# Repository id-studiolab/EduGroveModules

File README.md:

# EduGroveModules

A collection of Grove-compatible modules, designed specifically for educational needs. 

<div style="display: flex; flex-direction: row; flex-wrap: wrap; justify-content: center;">

  </a>
    
  </a>
    
</div>

## Grove-Compatible Modules for Education

These designs are tailored for use in the [**Connected Interaction Kit**](https://id-studiolab.github.io/Connected-Interaction-Kit) and beyond, offering specific functionalities and optimizations to enhance hands-on learning in tech and design education.

## Modules Overview

### [**Custom Component Board**](CustomComponents/README.md)

A versatile 2x3 cm PCB for easy assembly and interfacing of common sensors, demanding basic soldering skills. Useful for educational soldering practices.

### [**Time-of-Flight Distance Sensor**](Time-of-Flight/README.md)

Cost-effective, Grove-compatible boards for the VL53L0X sensor, enabling precise distance measurements up to 2 meters.

### [**ChaiNEO**](ChaiNEO/README.md)

Daisy-chainable, Grove-compatible boards designed for Neopixel-compatible LEDs.

### [**Motor Driver**](MotorDriver/README.md)

Simple I2C motor driver for servo,DC, and stepper motors.

### [**High power Neopixel**](HighPowerNEO/README.md)

A 12W neopixel with extra white chip for accurate color reproduction.

### [**Presence Sensor**](RadarSensor/README.md)

An adapter board for the LD2410 or LD2450 to make it Grove compatible for the Itsy Bitsy.

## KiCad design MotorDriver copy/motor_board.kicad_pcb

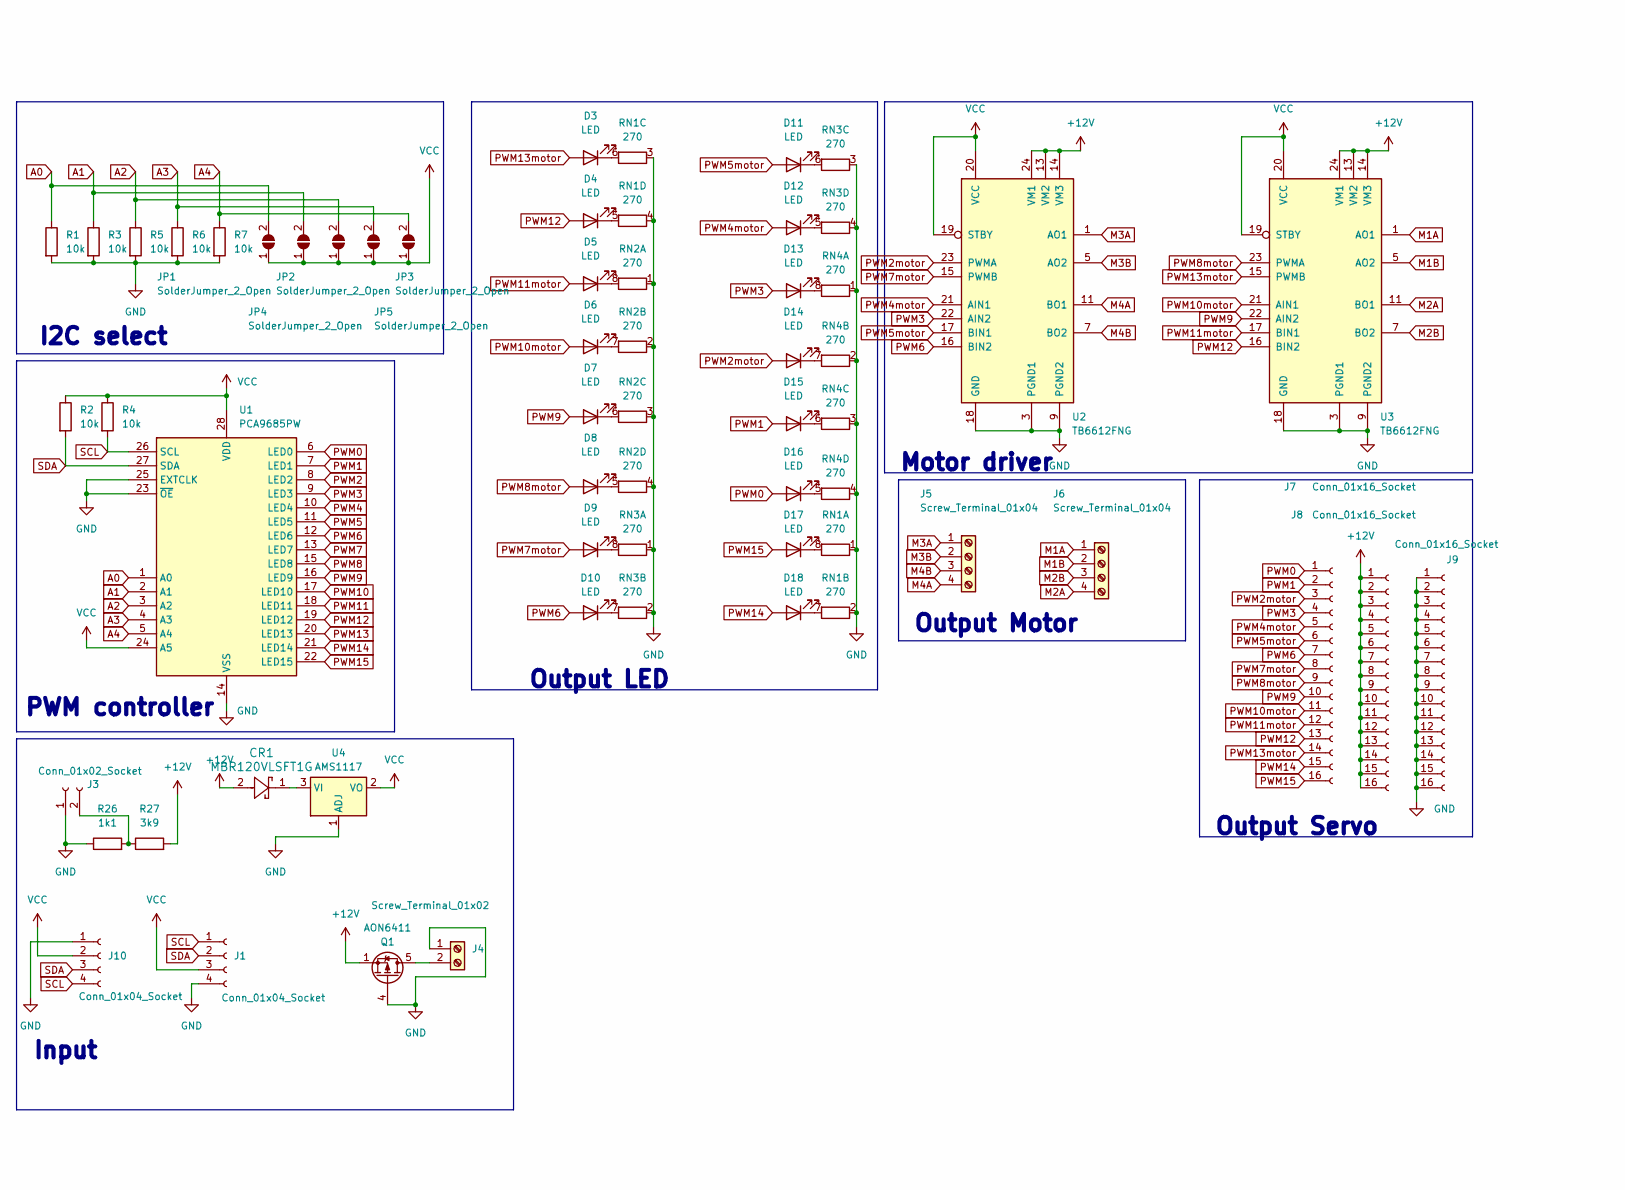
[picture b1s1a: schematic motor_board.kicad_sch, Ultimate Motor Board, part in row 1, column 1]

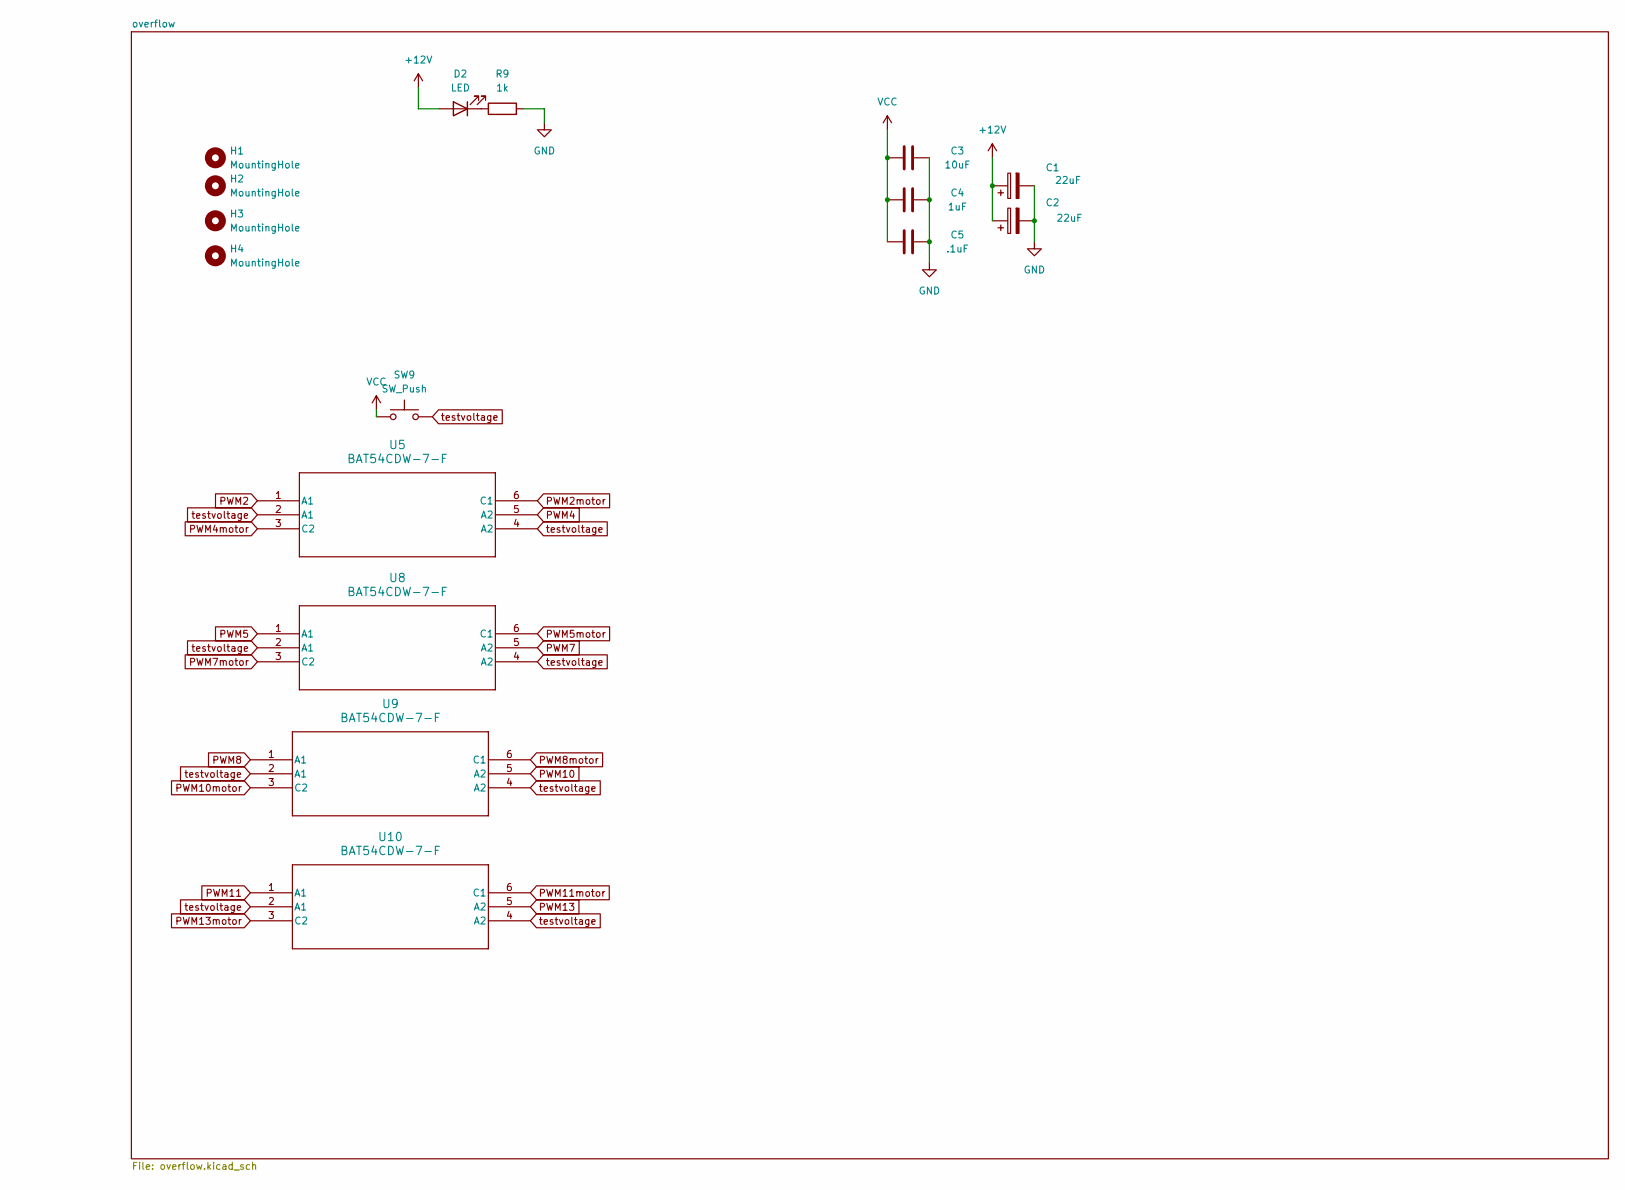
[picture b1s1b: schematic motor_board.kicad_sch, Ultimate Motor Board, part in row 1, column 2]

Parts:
C1, C2: 22uF; CP_Elec_6.3x5.7
C3: 10uF; C_0805_2012Metric_Pad1.18x1.45mm_HandSolder
C4: 1uF; C_0805_2012Metric_Pad1.18x1.45mm_HandSolder
C5: .1uF; C_0805_2012Metric_Pad1.18x1.45mm_HandSolder
CR1: MBR120VLSFT1G; SDO_SOD-123FL_ONS
D2, D3, D4, D5, D6, D7, D8, D9, D10, D11, D12, D13, D14, D15, D16, D17, D18: LED; LED_0805_2012Metric_Pad1.15x1.40mm_HandSolder
H1, H2, H3, H4: MountingHole; MountingHole_2.5mm
J1: Conn_01x04_Socket; NS-Tech_Grove_1x04_P2mm_Vertical
J3: Conn_01x02_Socket; PinHeader_1x02_P2.54mm_Vertical
J4: Screw_Terminal_01x02; TerminalBlock_Phoenix_PT-1,5-2-5.0-H_1x02_P5.00mm_Horizontal
J5, J6: Screw_Terminal_01x04; TerminalBlock_Phoenix_PT-1,5-4-5.0-H_1x04_P5.00mm_Horizontal
J7, J8, J9: Conn_01x16_Socket; PinHeader_1x16_P2.54mm_Vertical
J10: Conn_01x04_Socket; JST_SH_SM04B-SRSS-TB_1x04-1MP_P1.00mm_Horizontal
JP1, JP2, JP3, JP4, JP5: SolderJumper_2_Open; SolderJumper-2_P1.3mm_Open_TrianglePad1.0x1.5mm
Q1: AON6411; AO_DFN-8-1EP_5.55x5.2mm_P1.27mm_EP4.12x4.6mm
R1, R2, R3, R4, R5, R6, R7: 10k; R_0805_2012Metric_Pad1.20x1.40mm_HandSolder
R9: 1k; R_0805_2012Metric_Pad1.20x1.40mm_HandSolder
R26: 1k1; R_0805_2012Metric_Pad1.20x1.40mm_HandSolder
R27: 3k9; R_0805_2012Metric_Pad1.20x1.40mm_HandSolder
RN1, RN2, RN3, RN4: 270; R_Array_Convex_4x1206
SW9: SW_Push; SW_Push_SPST_NO_Alps_SKRK
U1: PCA9685PW; TSSOP-28_4.4x9.7mm_P0.65mm
U2, U3: TB6612FNG; SSOP-24_5.3x8.2mm_P0.65mm
U4: AMS1117; SOT-223-3_TabPin2
U5, U8, U9, U10: BAT54CDW-7-F; SOT-363_DIO

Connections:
+12V: C1.1, C2.1, CR1.2, D2.2 (A), J8.1, J8.2, J8.3, J8.4, J8.5, J8.6, J8.7, J8.8, J8.9, J8.10, J8.11, J8.12, J8.13, J8.14, J8.15, J8.16, Q1.1 (S), Q1.2 (S), Q1.3 (S), R27.2, U2.13 (VM2), U2.14 (VM3), U2.24 (VM1), U3.13 (VM2), U3.14 (VM3), U3.24 (VM1)
A0: JP1.2 (B), R1.1, U1.1 (A0)
A1: JP2.2 (B), R3.1, U1.2 (A1)
A2: JP3.2 (B), R5.1, U1.3 (A2)
A3: JP4.2 (B), R6.1, U1.4 (A3)
A4: JP5.2 (B), R7.1, U1.5 (A4)
GND: C1.2, C2.2, C3.2, C4.2, C5.2, J1.4, J3.1, J4.1, J9.1, J9.2, J9.3, J9.4, J9.5, J9.6, J9.7, J9.8, J9.9, J9.10, J9.11, J9.12, J9.13, J9.14, J9.15, J9.16, J10.1, Q1.4 (G), R1.2, R3.2, R5.2, R6.2, R7.2, R9.2, R26.1, RN1.1 (R1.1), RN1.2 (R2.1), RN1.3 (R3.1), RN1.4 (R4.1), RN2.1 (R1.1), RN2.2 (R2.1), RN2.3 (R3.1), RN2.4 (R4.1), RN3.1 (R1.1), RN3.2 (R2.1), RN3.3 (R3.1), RN3.4 (R4.1), RN4.1 (R1.1), RN4.2 (R2.1), RN4.3 (R3.1), RN4.4 (R4.1), U1.14 (VSS), U1.23 (~OE), U1.25 (EXTCLK), U2.3 (PGND1), U2.4 (PGND1), U2.9 (PGND2), U2.10 (PGND2), U2.18 (GND), U3.3 (PGND1), U3.4 (PGND1), U3.9 (PGND2), U3.10 (PGND2), U3.18 (GND), U4.1 (ADJ)
M1A: J6.1, U3.1 (AO1), U3.2 (AO1)
M1B: J6.2, U3.5 (AO2), U3.6 (AO2)
M2A: J6.4, U3.11 (BO1), U3.12 (BO1)
M2B: J6.3, U3.7 (BO2), U3.8 (BO2)
M3A: J5.1, U2.1 (AO1), U2.2 (AO1)
M3B: J5.2, U2.5 (AO2), U2.6 (AO2)
M4A: J5.4, U2.11 (BO1), U2.12 (BO1)
M4B: J5.3, U2.7 (BO2), U2.8 (BO2)
unnamed: D2.1 (K), R9.1
unnamed: D3.1 (K), RN1.6 (R3.2)
unnamed: D4.1 (K), RN1.5 (R4.2)
unnamed: D5.1 (K), RN2.8 (R1.2)
unnamed: D6.1 (K), RN2.7 (R2.2)
unnamed: D7.1 (K), RN2.6 (R3.2)
unnamed: D8.1 (K), RN2.5 (R4.2)
unnamed: D9.1 (K), RN3.8 (R1.2)
unnamed: D10.1 (K), RN3.7 (R2.2)
unnamed: D11.1 (K), RN3.6 (R3.2)
unnamed: D12.1 (K), RN3.5 (R4.2)
unnamed: D13.1 (K), RN4.8 (R1.2)
unnamed: D14.1 (K), RN4.7 (R2.2)
unnamed: D15.1 (K), RN4.6 (R3.2)
unnamed: D16.1 (K), RN4.5 (R4.2)
unnamed: D17.1 (K), RN1.8 (R1.2)
unnamed: D18.1 (K), RN1.7 (R2.2)
unnamed: J3.2, R26.2, R27.1
unnamed: J4.2, Q1.5 (D)
unnamed: CR1.1, U4.3 (VI)
PWM0: D16.2 (A), J7.1, U1.6 (LED0)
PWM1: D15.2 (A), J7.2, U1.7 (LED1)
PWM2: U1.8 (LED2), U5.1 (A1)
PWM2motor: D14.2 (A), J7.3, U2.23 (PWMA), U5.6 (C1)
PWM3: D13.2 (A), J7.4, U1.9 (LED3), U2.22 (AIN2)
PWM4: U1.10 (LED4), U5.5 (A2)
PWM4motor: D12.2 (A), J7.5, U2.21 (AIN1), U5.3 (C2)
PWM5: U1.11 (LED5), U8.1 (A1)
PWM5motor: D11.2 (A), J7.6, U2.17 (BIN1), U8.6 (C1)
PWM6: D10.2 (A), J7.7, U1.12 (LED6), U2.16 (BIN2)
PWM7: U1.13 (LED7), U8.5 (A2)
PWM7motor: D9.2 (A), J7.8, U2.15 (PWMB), U8.3 (C2)
PWM8: U1.15 (LED8), U9.1 (A1)
PWM8motor: D8.2 (A), J7.9, U3.23 (PWMA), U9.6 (C1)
PWM9: D7.2 (A), J7.10, U1.16 (LED9), U3.22 (AIN2)
PWM10: U1.17 (LED10), U9.5 (A2)
PWM10motor: D6.2 (A), J7.11, U3.21 (AIN1), U9.3 (C2)
PWM11: U1.18 (LED11), U10.1 (A1)
PWM11motor: D5.2 (A), J7.12, U3.17 (BIN1), U10.6 (C1)
PWM12: D4.2 (A), J7.13, U1.19 (LED12), U3.16 (BIN2)
PWM13: U1.20 (LED13), U10.5 (A2)
PWM13motor: D3.2 (A), J7.14, U3.15 (PWMB), U10.3 (C2)
PWM14: D18.2 (A), J7.15, U1.21 (LED14)
PWM15: D17.2 (A), J7.16, U1.22 (LED15)
SCL: J1.1, J10.4, R4.2, U1.26 (SCL)
SDA: J1.2, J10.3, R2.2, U1.27 (SDA)
VCC: C3.1, C4.1, C5.1, J1.3, J10.2, JP1.1 (A), JP2.1 (A), JP3.1 (A), JP4.1 (A), JP5.1 (A), R2.1, R4.1, SW9.1, U1.24 (A5), U1.28 (VDD), U2.19 (STBY), U2.20 (VCC), U3.19 (STBY), U3.20 (VCC), U4.2 (VO)
testvoltage: SW9.2, U5.2 (A1), U5.4 (A2), U8.2 (A1), U8.4 (A2), U9.2 (A1), U9.4 (A2), U10.2 (A1), U10.4 (A2)

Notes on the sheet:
Output Servo
Motor driver
Input
Output LED
Output Motor
I2C select
PWM controller

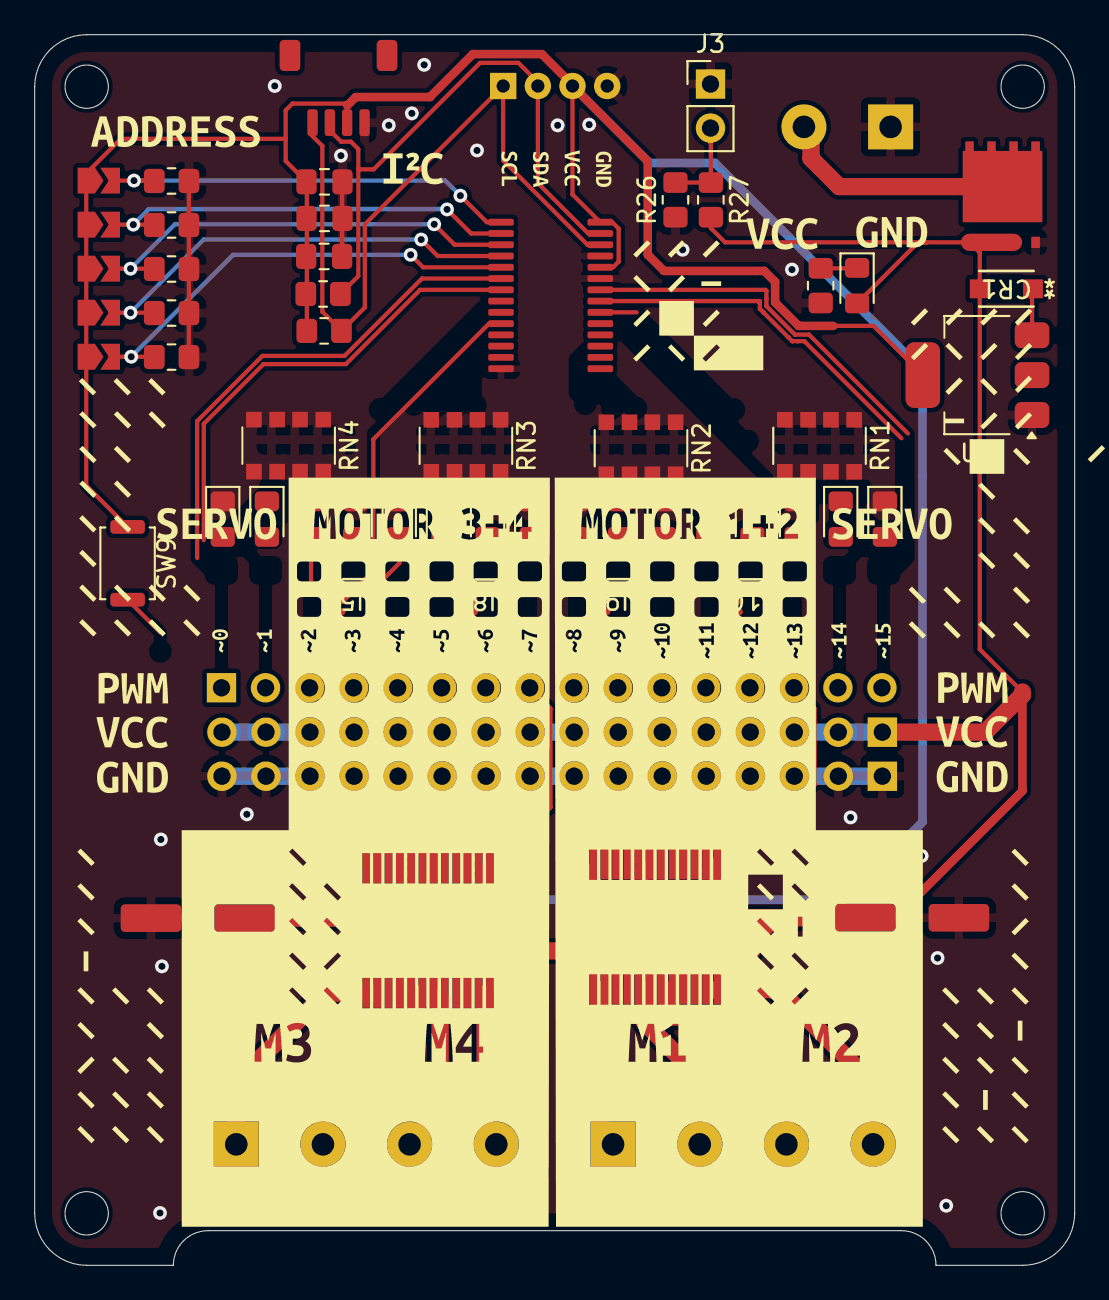
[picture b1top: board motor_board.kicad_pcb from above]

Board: 2 copper layers, 60.0 x 71.0 mm, 65 parts (0 on the bottom side), 63 nets.

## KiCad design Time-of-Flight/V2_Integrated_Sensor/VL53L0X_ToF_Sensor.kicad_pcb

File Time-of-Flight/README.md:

# Time-of-Flight Distance Sensor (VL53L0X)

Grove-Compatible Time-of-Flight Sensor Boards using the VL53L0X sensor

Two cost-effective, Grove-compatible board designs for the VL53L0X Time-of-Flight (ToF) sensor.

## Version 1

A compact adapter board that facilitates the use of a cost-effective, widely-available 6-pin breakout design for the VL53L0X sensor with the Grove ecosystem.

- **Type**: Adapter Board
- **Size**: 16 x 16 mm
- **Mounting**: Provided by the original breakout board

## Version 2

A slightly larger board that natively incorporates the VL53L0X sensor into its design.

- **Type**: Integrated Sensor Board
- **Size**: 20 x 20 mm
- **Mounting**: Two 2.75mm diameter mounting holes along the top edge

## Additional Resources and Instructions

Further resources and usage instructions for the ToF sensor boards can be explored in detail [here](https://id-studiolab.github.io/Connected-Interaction-Kit/components/time-of-flight-distance-sensor/time-of-flight-distance-sensor.html).

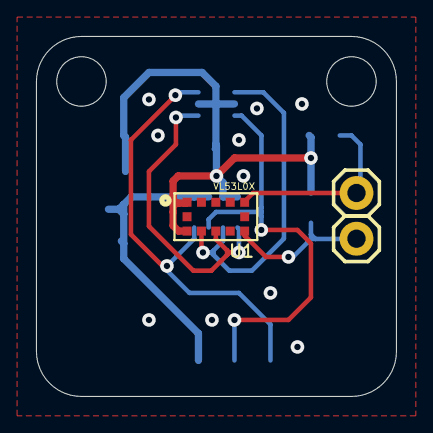
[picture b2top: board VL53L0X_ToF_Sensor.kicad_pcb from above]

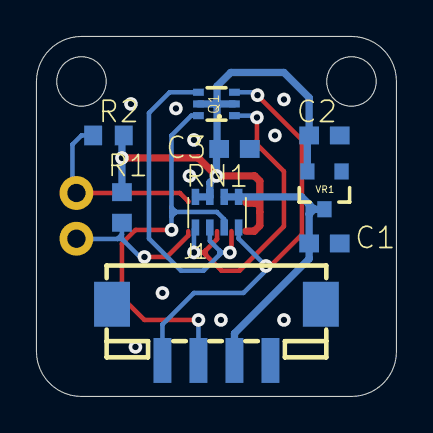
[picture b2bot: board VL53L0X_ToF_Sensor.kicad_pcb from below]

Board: 2 copper layers, 20.0 x 20.0 mm, 14 parts (9 on the bottom side), 9 nets.

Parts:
C1, C2: 10µF; C0603
C3: 0.1µF; C0603
J1: H4P-SMD-2.0; HW4-SMD-2.0
JP1, JP2: M01PTH; 1X01
Q1: BSS138DW; SOT363
R1, R2: 10k; R0603
RN1: 10k; CAY1647R0F4LF
U1: VL53L0X; LGA12_ST
UNK_HOLE_0: dummyfp0
UNK_HOLE_1: dummyfp1
VR1: SOT23-3

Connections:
2.8V: C2.1, C3.1, Q1.2, Q1.5, R1.2, R2.2, RN1.3, RN1.4, U1.1, U1.11, VR1.2
GND: C1.2, C2.2, C3.2, J1.4, J1.SS1, J1.SS2, U1.2, U1.3, U1.4, U1.6, U1.12, VR1.1
GPIO: JP1.1, R1.1, U1.7
SCL: J1.1, Q1.3, RN1.8
SCL_2.8V: Q1.4, RN1.6, U1.10
SDA: J1.2, Q1.6, RN1.7
SDA_2.8V: Q1.1, RN1.5, U1.9
VIN: C1.1, J1.3, RN1.1, RN1.2, VR1.3
XSHUT: JP2.1, R2.1, U1.5

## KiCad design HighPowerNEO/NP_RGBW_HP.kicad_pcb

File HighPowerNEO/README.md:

# High Power RGBW Neopixel
A 12W neopixel with extra white chip for accurate color reproduction.
It uses the UCS2904B chip to toggle the channels, can be programmed simiarly to the SK6812 chip

# Design Features
This 40x81mm PCB (aluminium PCB required for heat reduction) connects 3 high power RGBW leds in series. This makes it possible for you to power it by 12v and will get you a lot of light. it makes it possible to light up entire rooms!
It uses standard 12v neopixel strip connectors to daisy chain them together.

# Files and Documentation
Schematic files and additional documentation are available in the Production Files subdirectory.

# Code example
```
# --- Imports
import time
import board
import neopixel

# --- Variables
pin_leds = board.D13

num_leds = 3
leds = neopixel.NeoPixel(pin_leds, num_leds, auto_write=False, pixel_order=neopixel.GRBW)

# --- Functions

# --- Setup
leds.fill(0) # turn off all LEDs
leds.show()

# --- Main loop
while True:
    
    # set color values for the LEDs individually
    leds[0] = (255, 0, 0, 0) # red
    leds[1] = (0, 255, 0, 0) # green
    leds[2] = (0, 0, 255, 0) # blue
    leds.show()
    time.sleep(2)
    
    # make LEDs white
    leds.fill((0, 0, 0, 255)) # white
    leds.show()
    
    time.sleep(2)

```

# IMPORTANT: 
At this point in time we are still checking the thermals of this design, it might get a bit hot so if you reproduce this you want to propperly cool the PCB

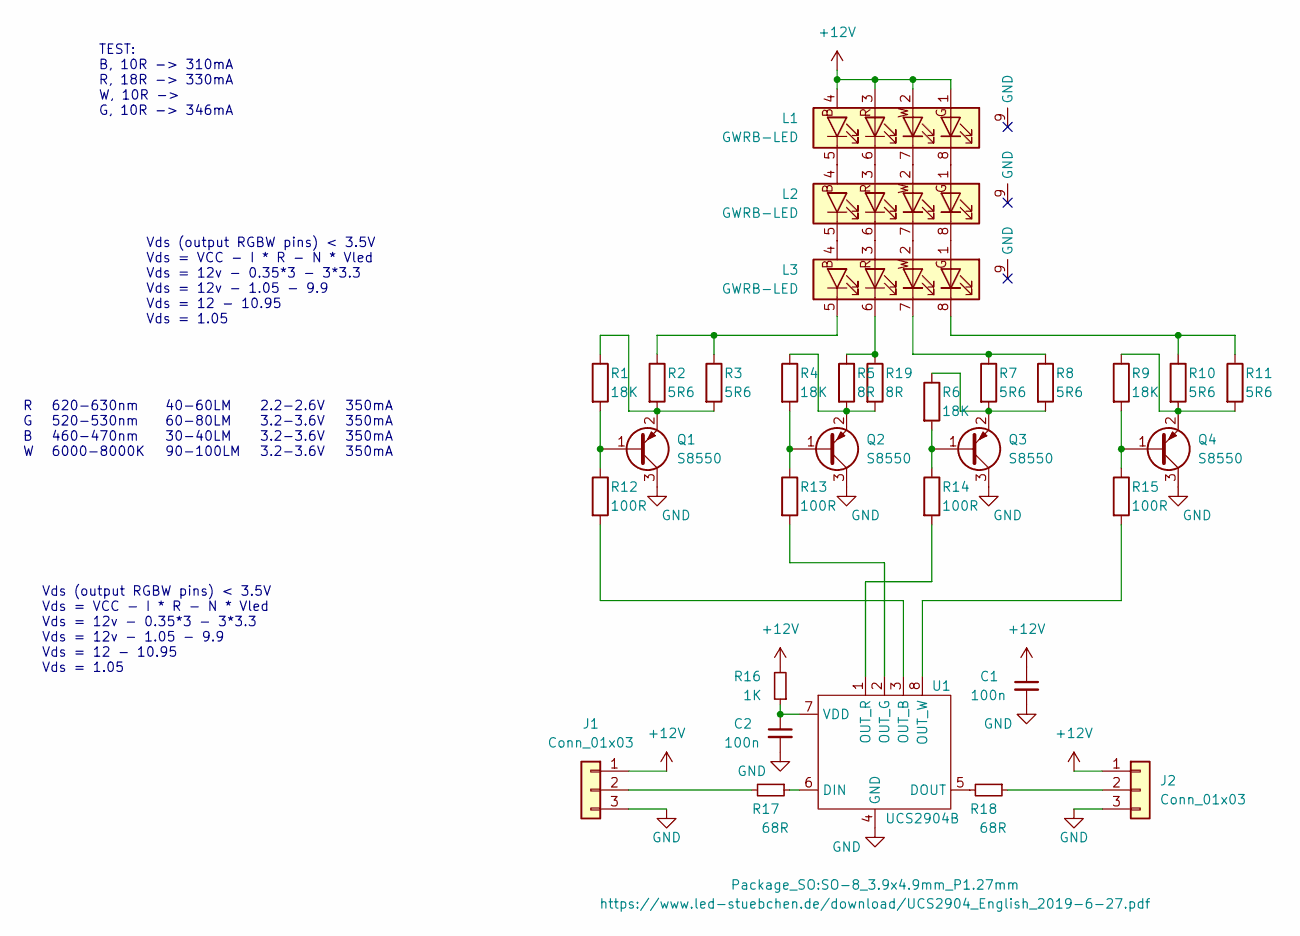
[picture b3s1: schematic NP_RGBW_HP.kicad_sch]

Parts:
C1: 100n; C_1206_3216Metric
C2: 100n; C_0805_2012Metric
J1, J2: Conn_01x03; SolderWirePad_1x01_SMD_5x10mm
L1, L2, L3: GWRB-LED; LED_BEAD_8P
Q1, Q2, Q3, Q4: S8550; SOT-23
R1, R4, R6, R9: 18K; R_0805_2012Metric
R2, R3, R7, R8, R10, R11: 5R6; R_1206_3216Metric
R5, R19: 8R; R_1206_3216Metric
R12, R13, R14, R15: 100R; R_0805_2012Metric
R16: 1K; R_0805_2012Metric
R17, R18: 68R; R_0805_2012Metric
U1: UCS2904B; SO-8_3.9x4.9mm_P1.27mm

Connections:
+12V: C1.1, J1.1, J2.1, L1.1, L1.2, L1.3, L1.4, R16.2
GND: C1.2, C2.2, J1.3, J2.3, Q1.3 (C), Q2.3 (C), Q3.3 (C), Q4.3 (C), U1.4 (GND)
unnamed: J1.2, R17.2
unnamed: J2.2, R18.1
unnamed: L1.5, L2.4
unnamed: L1.6, L2.3
unnamed: L1.7, L2.2
unnamed: L1.8, L2.1
unnamed: L2.5, L3.4
unnamed: L2.6, L3.3
unnamed: L2.7, L3.2
unnamed: L2.8, L3.1
unnamed: L3.5, R2.1, R3.1
unnamed: L3.6, R5.1, R19.1
unnamed: L3.7, R7.1, R8.1
unnamed: L3.8, R10.1, R11.1
unnamed: Q1.1 (B), R1.2, R12.1
unnamed: Q1.2 (E), R1.1, R2.2, R3.2
unnamed: Q2.1 (B), R4.2, R13.1
unnamed: Q2.2 (E), R4.1, R5.2, R19.2
unnamed: Q3.1 (B), R6.2, R14.1
unnamed: Q3.2 (E), R6.1, R7.2, R8.2
unnamed: Q4.1 (B), R9.2, R15.1
unnamed: Q4.2 (E), R9.1, R10.2, R11.2
unnamed: R17.1, U1.6 (DIN)
unnamed: R18.2, U1.5 (DOUT)
unnamed: R12.2, U1.3 (OUT_B)
unnamed: R13.2, U1.2 (OUT_G)
unnamed: R14.2, U1.1 (OUT_R)
unnamed: R15.2, U1.8 (OUT_W)
unnamed: C2.1, R16.1, U1.7 (VDD)

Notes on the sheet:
Vds (output RGBW pins) < 3.5V Vds = VCC - I * R - N * Vled Vds = 12v - 0.35*3 - 3*3.3 Vds = 12v - 1.05 - 9.9 Vds = 12 - 10.95 Vds = 1.05
2.2-2.6V 3.2-3.6V 3.2-3.6V 3.2-3.6V
40-60LM 60-80LM 30-40LM 90-100LM
R G B W
350mA 350mA 350mA 350mA
TEST: B, 10R -> 310mA R, 18R -> 330mA W, 10R -> G, 10R -> 346mA
620-630nm 520-530nm 460-470nm 6000-8000K

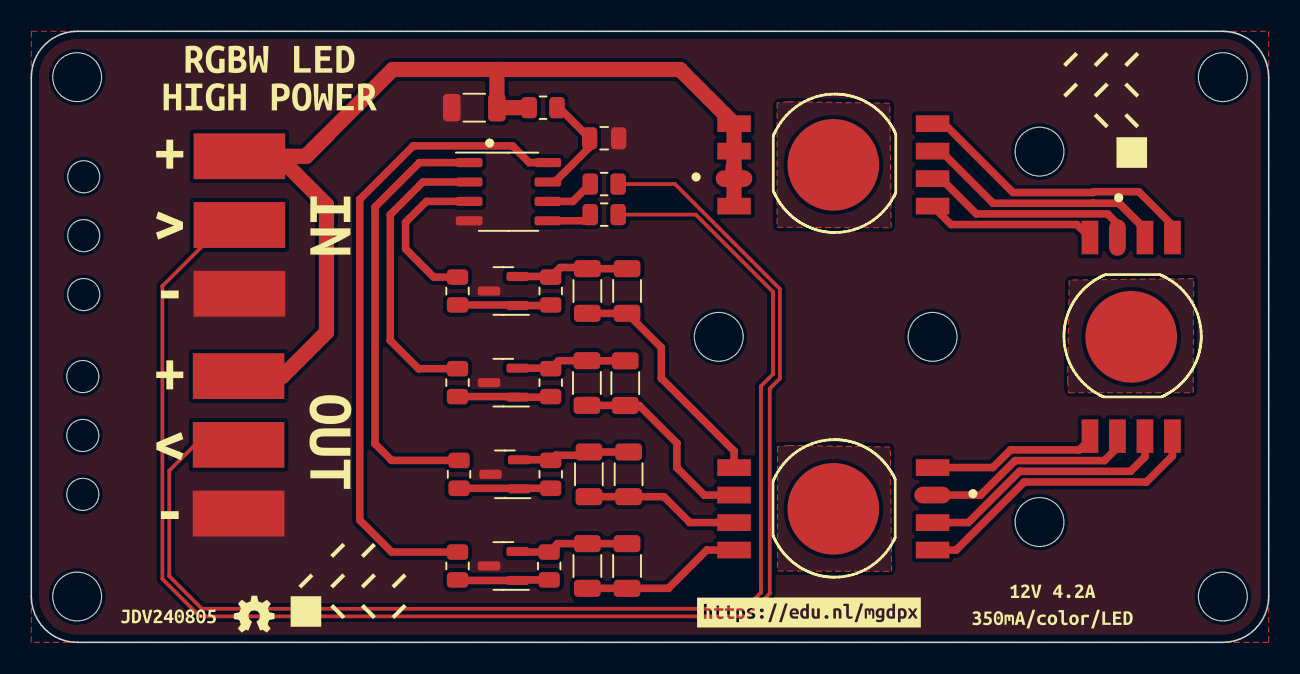
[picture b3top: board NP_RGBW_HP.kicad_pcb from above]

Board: 2 copper layers, 81.0 x 40.0 mm, 31 parts (0 on the bottom side), 31 nets.

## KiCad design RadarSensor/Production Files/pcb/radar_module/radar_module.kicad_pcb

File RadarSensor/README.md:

# Presence Sensor
An adapter board for the LD2410 or LD2450 to make it Grove compatible for the Itsy Bitsy! It has an integrated 5v boost circuit to power the radar sensors

# Design Features
This 50x25mm PCB makes it easy to interface with the LD2410 and LD2450 radar sensors, uart is directly routed to the corresponding pins. The 5v for the modules is created from the 3.3v supply with the help of the MIC2288 chip.

# Files and Documentation
Schematic files and additional documentation are available in the Production Files subdirectory.

# Code example
```
import time
import board
import busio
from ld2410 import LD2410

# Initialize UART for communication with the LD2410 sensor
uart = busio.UART(board.TX, board.RX, baudrate=256000)

# Create an instance of the LD2410 class
ld2410 = LD2410(uart)

# Read Firmware Version
ld2410.read_firmware_version()

# Wait for a moment
time.sleep(1)

def main():
    while True:
        # Update the sensor data
        ld2410.update()
        
        # Print out the parsed data
        print("Target State:", ld2410.target_state)
        print("Moving Distance:", ld2410.moving_distance, "cm")
        print("Moving Energy:", ld2410.moving_energy)
        print("Stationary Distance:", ld2410.stationary_distance, "cm")
        print("Stationary Energy:", ld2410.stationary_energy)
        print("Detection Distance:", ld2410.detection_distance, "cm")
        print("-" * 40)
        
        # Delay before the next update
        time.sleep(5)

if __name__ == "__main__":
    main()
```

# Status
This project is still in development.

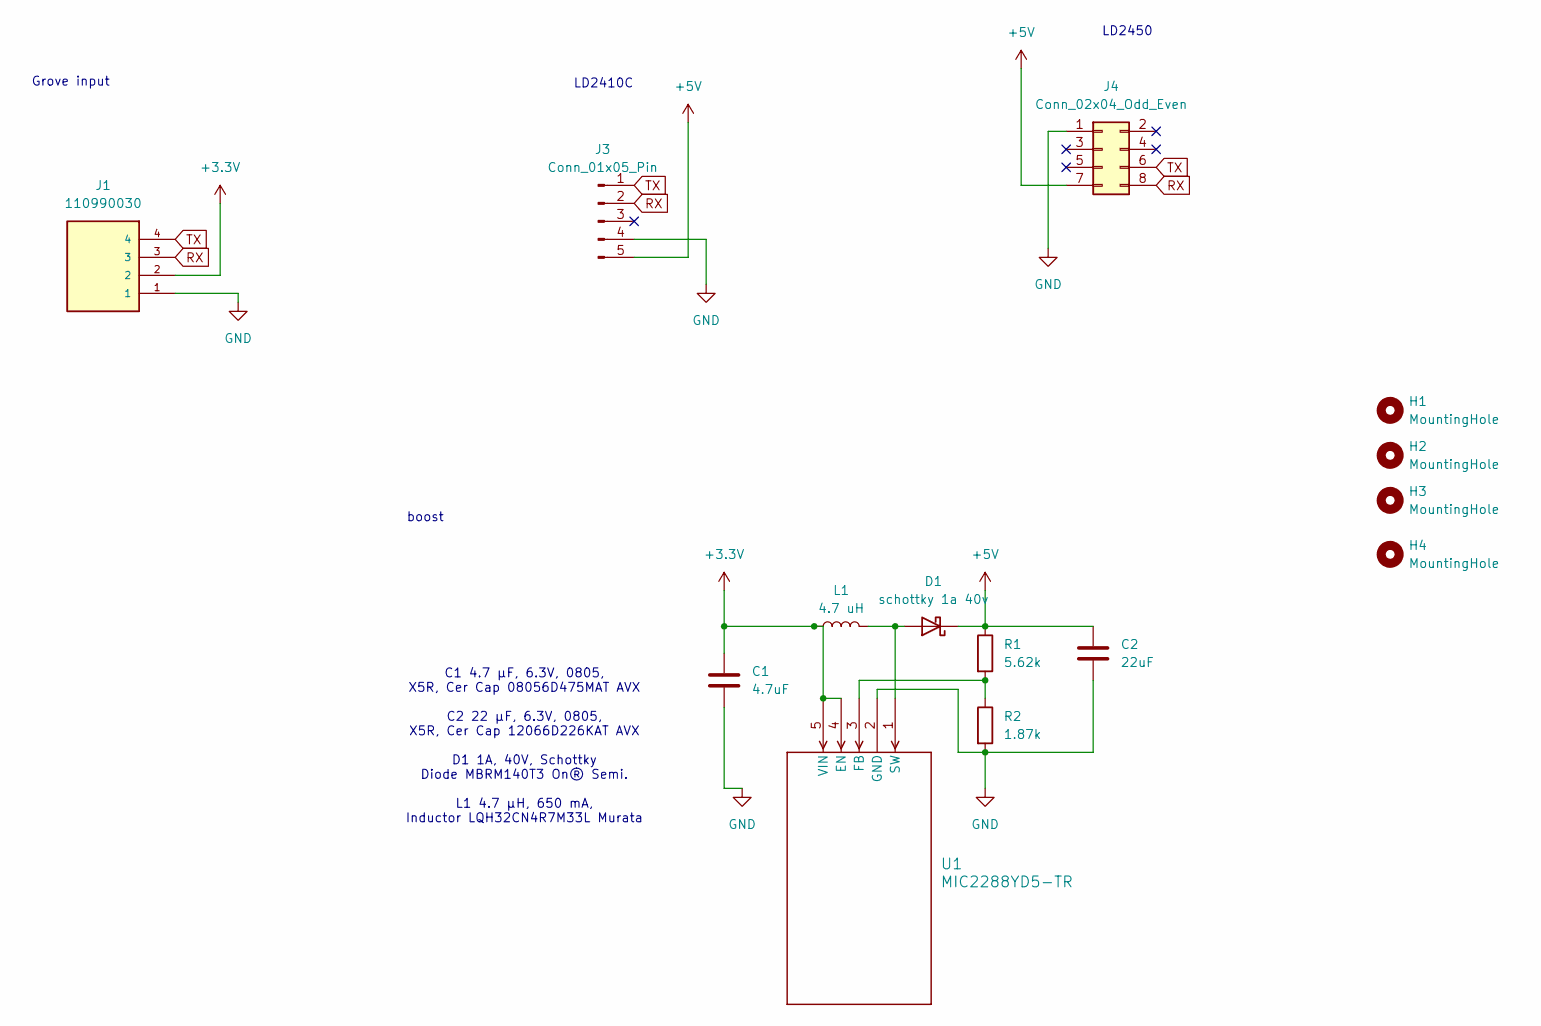
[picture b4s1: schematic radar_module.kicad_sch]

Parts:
C1: 4.7uF; C_0805_2012Metric_Pad1.18x1.45mm_HandSolder
C2: 22uF; C_0805_2012Metric_Pad1.18x1.45mm_HandSolder
D1: schottky 1a 40v; D_2114_3652Metric_Pad1.85x3.75mm_HandSolder
H1, H2, H3, H4: MountingHole; MountingHole_3.2mm_M3
J1: 110990030; SEEED_110990030; PARTREV A
J3: Conn_01x05_Pin; PinHeader_1x05_P2.54mm_Vertical
J4: Conn_02x04_Odd_Even; PinSocket_2x04_P2.00mm_Vertical
L1: 4.7 uH; L_TDK_SLF6045
R1: 5.62k; R_0805_2012Metric_Pad1.20x1.40mm_HandSolder
R2: 1.87k; R_0805_2012Metric_Pad1.20x1.40mm_HandSolder
U1: MIC2288YD5-TR; TSOT-23-5_D5_MCH

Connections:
+3.3V: C1.1, J1.2, L1.1, U1.4 (EN), U1.5 (VIN)
+5V: C2.1, D1.1 (K), J3.5, J4.7, R1.1
GND: C1.2, C2.2, J1.1, J3.4, J4.1, R2.2, U1.2 (GND)
unnamed: D1.2 (A), L1.2, U1.1 (SW)
unnamed: R1.2, R2.1, U1.3 (FB)
RX: J1.3, J3.2, J4.8
TX: J1.4, J3.1, J4.6

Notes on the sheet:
LD2450
Grove input
C1 4.7 µF, 6.3V, 0805, X5R, Cer Cap 08056D475MAT AVX C2 22 µF, 6.3V, 0805, X5R, Cer Cap 12066D226KAT AVX D1 1A, 40V, Schottky Diode MBRM140T3 On® Semi. L1 4.7 µH, 650 mA, Inductor LQH32CN4R7M33L Murata
LD2410C
boost

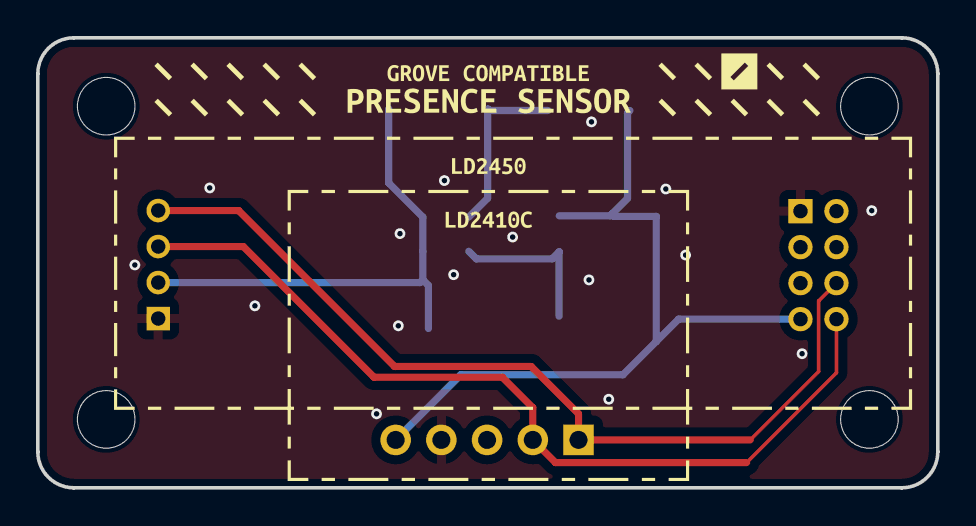
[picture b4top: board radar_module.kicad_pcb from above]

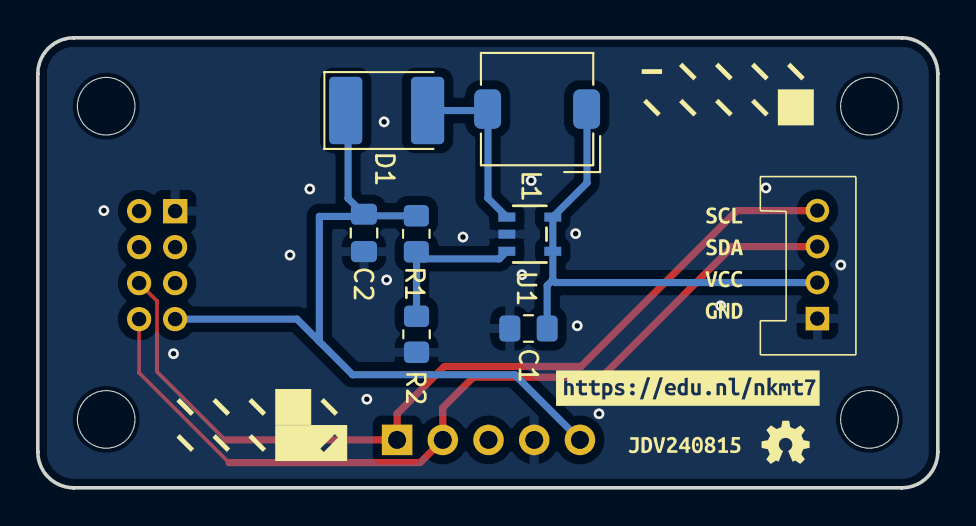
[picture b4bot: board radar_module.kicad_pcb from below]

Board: 2 copper layers, 50.0 x 25.0 mm, 14 parts (9 on the bottom side), 7 nets.

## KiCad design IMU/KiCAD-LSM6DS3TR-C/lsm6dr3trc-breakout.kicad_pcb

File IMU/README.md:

# IMU sensor based on LSM6SDS3TR

Grove-Compatible IMU Sensor board using the LSM6SDS3TR sensor

## Background

The LSM6DS3 is a 6-axis inertial measurement unit (IMU) that combines a 3-axis accelerometer and 3-axis gyroscope. It communicates via I2C and provides real-time motion data with low power consumption. The sensor is commonly used in robotics and IoT applications for motion detection, orientation tracking, and gesture recognition. The LSM6DS3TRC variant used here is optimized for embedded systems and offers high accuracy with configurable measurement ranges.

- **Type**: Integrated Sensor Board
- **Size**: 20 x 30 mm
- **Mounting**: Four 2.75mm diameter mounting holes along the top edge

## Usage Example
```python
import time
import board
from adafruit_lsm6ds.lsm6dsox import LSM6DSOX

i2c = board.I2C()  # uses board.SCL and board.SDA
sox = LSM6DSOX(i2c, address=0x6B)

while True:
    print("Acceleration: X:%.2f, Y: %.2f, Z: %.2f m/s^2"%(sox.acceleration))
    print("Gyro X:%.2f, Y: %.2f, Z: %.2f radians/s"%(sox.gyro))
    print("")
    time.sleep(0.5)
```
## Fusion Library
Jordan Boyle made a Circuitpython fusion library for the sensor providing:
-  Quaternion-based complementary filter for fusing accelerometer and gyroscope data.
-  Euler angle outputs (roll, pitch, yaw) and angular rates on demand.

It can be found [here](/IMU/fusionlibrary)

## Additional Resources and Instructions

Further resources and usage instructions for the IMU sensor boards can be explored in detail [here](https://id-studiolab.github.io/Connected-Interaction-Kit/components/imu-sensor/imu-sensor.html).

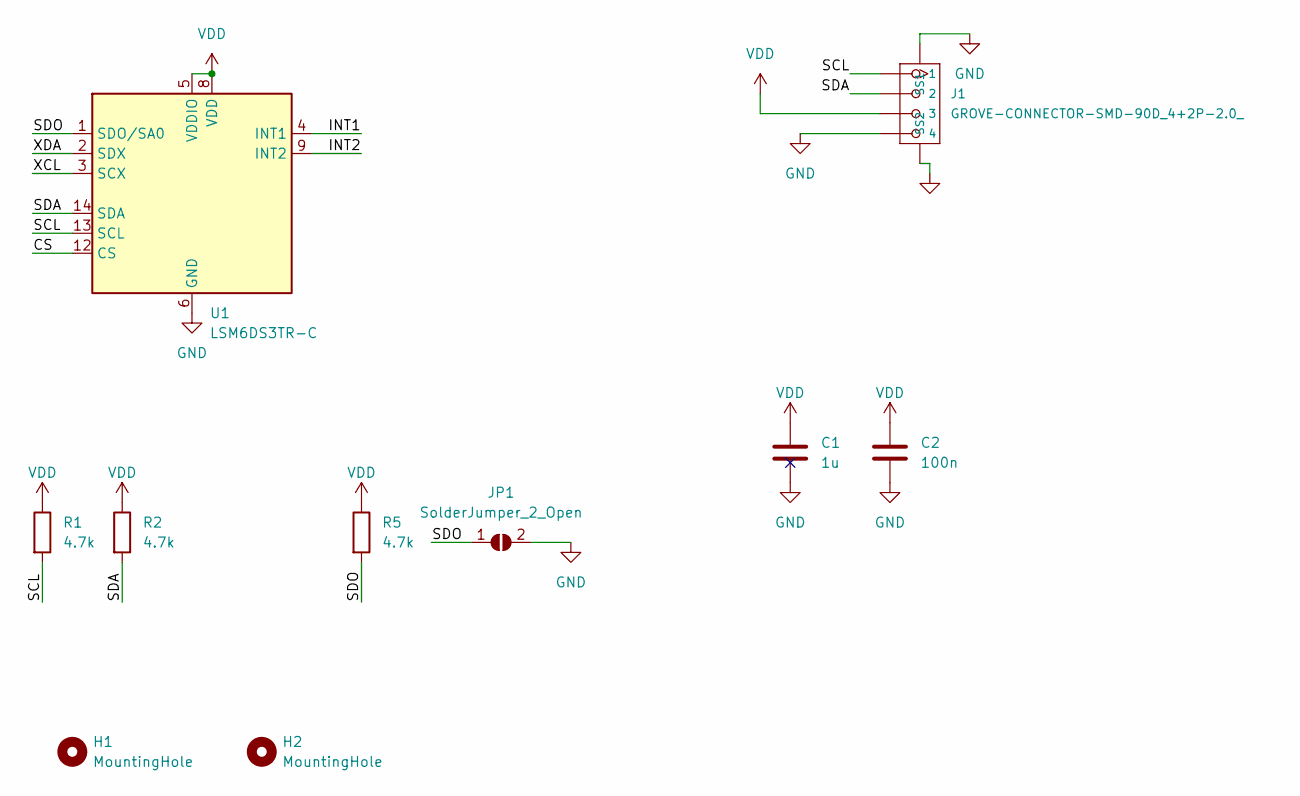
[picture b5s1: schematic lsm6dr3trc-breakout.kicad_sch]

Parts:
C1: 1u; C_0603_1608Metric
C2: 100n; C_0402_1005Metric
H1, H2: MountingHole; MountingHole_2.2mm_M2
J1: GROVE-CONNECTOR-SMD-90D_4+2P-2.0_; GROVE-HW4-SMD-2.0-90D
JP1: SolderJumper_2_Open; SolderJumper-2_P1.3mm_Open_TrianglePad1.0x1.5mm
R1, R2, R5: 4.7k; R_0402_1005Metric
U1: LSM6DS3TR-C; LGA-14_3x2.5mm_P0.5mm_LayoutBorder3x4y

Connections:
/CS: U1.12 (CS)
/INT1: U1.4 (INT1)
/INT2: U1.9 (INT2)
/SCL: J1.1, R1.2, U1.13 (SCL)
/SDA: J1.2, R2.2, U1.14 (SDA)
/SDO: JP1.1 (A), R5.2, U1.1 (SDO/SA0)
/XCL: U1.3 (SCX)
/XDA: U1.2 (SDX)
GND: C1.2, C2.2, J1.4, J1.5 (SS1), J1.6 (SS2), JP1.2 (B), U1.6 (GND), U1.7 (GND)
VDD: C1.1, C2.1, J1.3, R1.1, R2.1, R5.1, U1.5 (VDDIO), U1.8 (VDD)

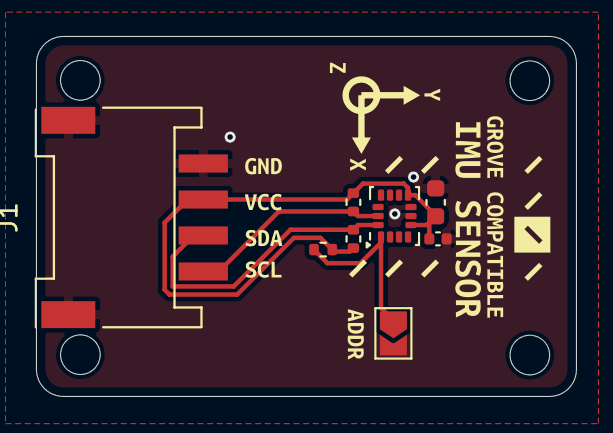
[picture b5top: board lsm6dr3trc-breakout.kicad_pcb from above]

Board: 2 copper layers, 30.0 x 20.0 mm, 12 parts (0 on the bottom side), 5 nets.

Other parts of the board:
H1#2, H2#2: MountingHole; MountingHole_2.2mm_M2

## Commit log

2023-10-03 Add ChaiNEO
2023-10-04 Readme
2023-10-04 Add ToF Sensor
2023-10-04 Add ToF Sensor v1 png
2023-10-04 Add Custom Component Boards
2024-04-24 Add first version of MotorDriver
2024-04-24 update main readme
2024-04-24 images next to eachother
2024-06-06 v2 of the motor driver
2024-06-06 add first version of High Power Neopixel
2024-06-06 typo
2024-06-13 more code examples or documentation
2024-06-13 add license
2024-08-05 first init radar sensor
2024-08-06 silkscreen for radar sensor, more code examples, better readme
2024-09-02 update radar module
2024-09-02 update high power neo
2024-09-02 update motor driver
2024-09-02 update chaineo
2024-09-02 update tof
2024-09-02 update readme radar sensor
2024-11-07 add drawing, example code, and library bundle
2025-11-11 added IMU
2025-11-11 correct folder name
2025-12-02 add info imu sensor
2026-01-23 cleanup
